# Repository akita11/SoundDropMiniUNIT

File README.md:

# SoundDropMiniUNIT

音声再生IC CH7800を使用した音声再生モジュールです。300KBのフラッシュメモリを搭載しており、PCにUSB Type-Cケーブルで接続するとUSBメモリとして認識され、そこにMP3音声データ等をコピーします。その音声データをGrove端子のシリアル(UART)通信で再生制御できます。UIFlow(v1)用のブロックもあります。

※CH7800に関する情報はWebページ等で検索してください。要点は以下にまとめてあります。

## 使い方（接続方法）

以下のようにスピーカやアンプを接続し、Grove端子からの制御で音声を再生します。
あわせて後述のcofig.txtでスピーカ出力（5文字目を"1"とする）に設定します（初期設定状態）。

### アンプ付きスピーカに接続する場合

3.5mmジャック（ステレオ：上部中央）に3.5mmステレオケーブル等でアンプに接続します。
あわせて後述のcofig.txtでDAC出力（5文字目を"0"とする）に設定します。

### スピーカを直接接続する場合

基板上部にある1.25mmピッチコネクタ(Molex 53047-0210用)をとりつける端子があり、市販の小型スピーカ（M5Stack本体に使われているものなど。AliExpressやTaobaoでも同等品があります）を接続することができます。※隙間がせまく差し込みにくいので注意してください。
あわせて後述のcofig.txtでスピーカ出力（5文字目を"1"とする）に設定します（初期設定状態）。

### 3.5mmジャックに直接スピーカを接続する方法

3.5mmジャックに直接スピーカを接続することもできます。その場合は、基板裏面のハンダジャンパを以下のように修正してください。（スピーカはモノラル再生となります）
※結線は、プラグの根本側から、GND-SPK-NC(無接続)、の順となります。そのため、ステレオ型スピーカではL側からの再生になります。またモノラルプラグでは、このGNDとSPKが短絡されるため使用できません。

- JP2をカット
- JP3・JP4の中央と△マーク側をカットし、中央と反対側（△マークがない側）をショート

## 本体機能の設定

PC接続時に現れるドライブ内の"config.txt"で、以下の機能を指定できます。
設定情報は、config.txtの1行目に、以下の7桁の数値を記載します（それ以降は無視される）。
- 1文字目: ボタンの動作。0=再生中に中断可、1=再生中に中断不可、2=リピート再生1、3=リピート再生2、4=ON/OFF、5=常時リピート再生
- 2-3文字目: 音量(00-30)
- 4文字目: BUSY端子の機能(1=アクティブL、0=アクティブH)
- 5文字目: 出力(1=PWM(スピーカ)、0=DAC)
- 6文字目: ボタンの信号極性(0=アクティブL、1=アクティブH)
- 7文字目: 0=通常動作、1=低電力モード 

初期設定として"0300100"（音量30、スピーカ出力、など）となっています。

## 使い方（ソフトウエア）

あらかじめ、本体基板の一部にあるUSB Type-CにUSB Type-Cケーブルを使ってPCへ接続し、現れるドライブに使用する音声データ（*.mp3）をコピーしておきます。なおファイル名は、「"001"から"999"の3桁の数値」のみが有効（CH7800の仕様）となり、その数値が「曲番号」となります。

### UIFlow(v1)での使い方

「SoundDropMini.m5b」をダウンロードし、UIFlow(v1)の"Custom"の"Open *.m5b"からこのファイルを指定すると、Init、Play、Stopの3つのブロックを使用できます。

※(25/04/21)内容にミスがありました。現在の修正済みファイルを使ってください。

- SoundDropMini_Init : 初期化。最初に1回だけ使用します。"TX"と"RX"には、使用するGroveポート・マイコン本体にあわせて、使用するピン番号を指定します。例えば、M5StackBasicのPortA（本体の赤いコネクタ）の場合は、上図のようにTX=21、RX=22を指定します。M5StackCore2のPortAの場合は、TX=32、RX=33となります。
- SoundDropMini_Play : numに指定した「曲番号」の音声を再生します。
- SoundDropMini_Stop : 再生中の音声を停止します。

※この例では再生した直後に停止していますので、音声がほぼ聞こえません。実際には目的に合わせて使い分けてください。

### その他のソフトウエアでの使い方

搭載されている音声再生IC(CH7800)のデータシート等を参考に、制御コマンドをUART経由で送信して使用してください。通信プロトコルは「9600bps/N81」です。
制御コマンドの一部を以下にまとめます。

- 次の曲の再生: 0x7e 0x11 0x00 0x02 0x00 0x00 0xef
- 前の曲の再生: 0x7e 0x12 0x00 0x02 0x00 0x00 0xef
- 指定した曲(HH:LL＝曲番号(上位/下位の順))の再生: 0x7e 0x13 0x00 0x02 HH LL 0xef
- 音量UP: 7e 0x14 0x00 0x02 0x00 0x00 0xef
- 音量DOWN: 0x7e 0x15 0x00 0x02 0x00 0x00 0xef
- 音量をNNに設定: 0x7e 0x16 0x00 0x02 0x00 NN 0xef
- 再生停止: 0x7e 0x26 0x00 0x02 0x00 0x00 0xef

## Author

Junichi Akita (@akita11) / akita@ifdl.jp

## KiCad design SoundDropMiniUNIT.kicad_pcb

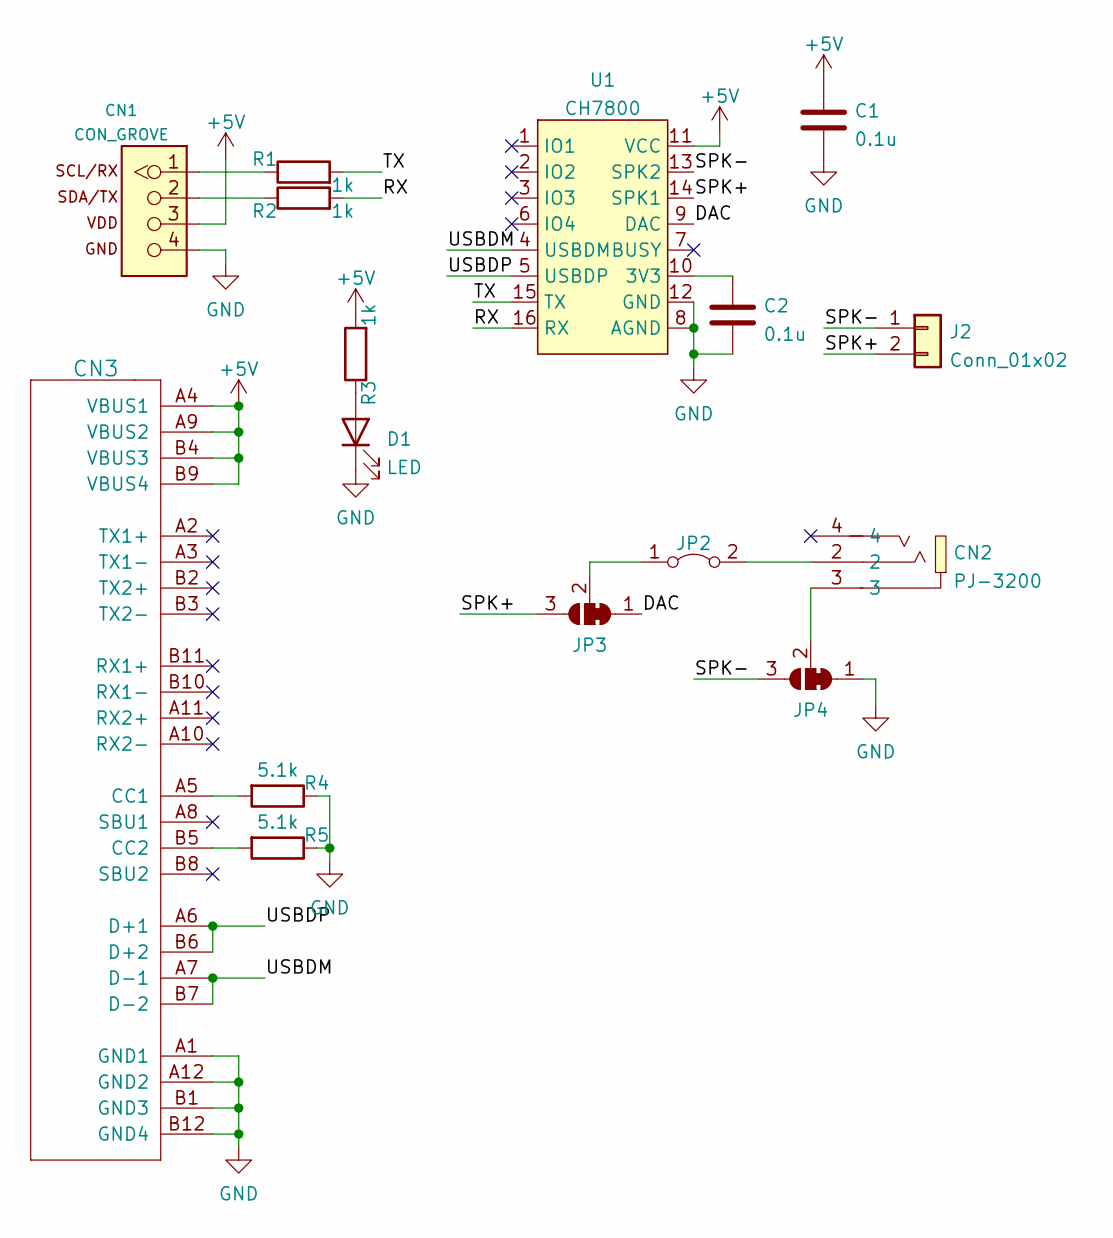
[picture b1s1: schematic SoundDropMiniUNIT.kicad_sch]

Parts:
C1, C2: 0.1u; C_0603_1608Metric
CN1: CON_GROVE; CON_GROVE_H
CN2: PJ-3200; AUDIO-TH_PJ-3200; LCSC Part C2689690
CN3: CON_USB-CPCBPLUG; USB-C_PCBPLUG
D1: LED; LED_0603_1608Metric
J2: Conn_01x02; Molex_PicoBlade_53047-0210_1x02_P1.25mm_Vertical
JP2: Jumper_2_Bridged; SolderJumper-2_P1.3mm_Bridged_Pad1.0x1.5mm
JP3, JP4: SolderJumper_3_Bridged12; SolderJumper-3_P1.3mm_Bridged12_Pad1.0x1.5mm
R1, R2, R3: 1k; R_0603_1608Metric
R4, R5: 5.1k; R_0603_1608Metric
U1: CH7800; SOP-16_4.4x10.4mm_P1.27mm

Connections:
+5V: C1.1, CN1.3, CN3.A4 (VBUS1), CN3.A9 (VBUS2), CN3.B4 (VBUS3), CN3.B9 (VBUS4), R3.2, U1.11 (VCC)
/DAC: JP3.1 (A), U1.9 (DAC)
/RX: R2.2, U1.16 (RX)
/SPK+: J2.2, JP3.3 (B), U1.14 (SPK1)
/SPK-: J2.1, JP4.3 (B), U1.13 (SPK2)
/TX: R1.2, U1.15 (TX)
/USBDM: CN3.A7 (D-1), CN3.B7 (D-2), U1.4 (USBDM)
/USBDP: CN3.A6 (D+1), CN3.B6 (D+2), U1.5 (USBDP)
GND: C1.2, C2.2, CN1.4, CN3.A1 (GND1), CN3.A12 (GND2), CN3.B1 (GND3), CN3.B12 (GND4), D1.1 (K), JP4.1 (A), R4.1, R5.1, U1.8 (AGND), U1.12 (GND)
unnamed: C2.1, U1.10 (3V3)
unnamed: CN1.1, R1.1
unnamed: CN1.2, R2.1
unnamed: CN2.2, JP2.2 (B)
unnamed: CN2.3, JP4.2 (C)
unnamed: CN3.A5 (CC1), R4.2
unnamed: CN3.B5 (CC2), R5.2
unnamed: D1.2 (A), R3.1
unnamed: JP2.1 (A), JP3.2 (C)

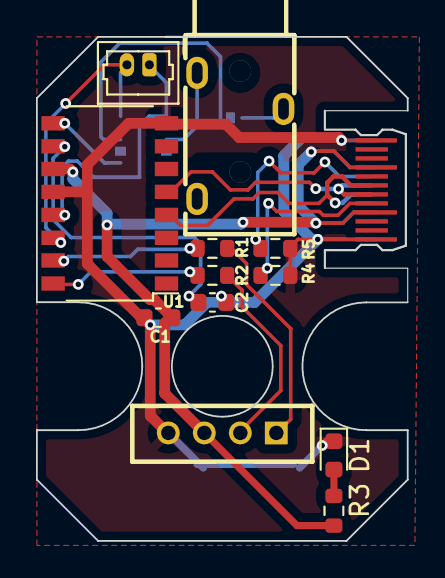
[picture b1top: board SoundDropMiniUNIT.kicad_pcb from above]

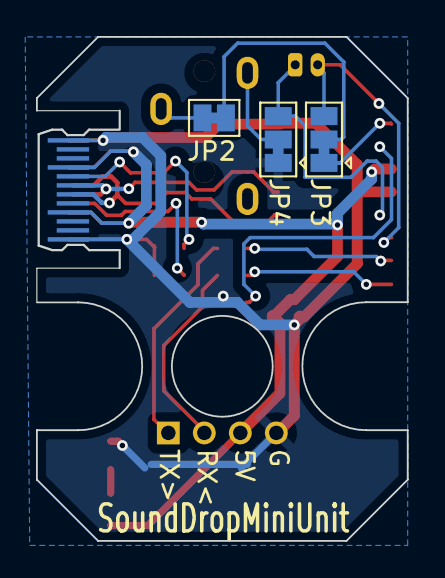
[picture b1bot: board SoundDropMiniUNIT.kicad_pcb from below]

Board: 2 copper layers, 20.6 x 28.0 mm, 16 parts (3 on the bottom side), 18 nets.

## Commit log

2025-03-18 intial commit, no photo
2025-03-22 add photo
2025-03-22 fix file name
2025-03-22 update UIFlow block
2025-03-22 fix UIFlow block
2026-04-09 Update README with speaker connection instructions
    Added instructions for connecting speakers directly to the 3.5mm jack.
